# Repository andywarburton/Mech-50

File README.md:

# Mech50
A 50% ortholinear mechanical keyboard PCB with three extra keys

** PLEASE FOR THE LOVE OF GOD DO NOT ORDER THIS KEYBOARD PCB, IT'S NOT TESTED. SEE NOTES BELOW !! ** 

Update: 14th October 2024

 * Uploaded QMK Firmware

To fix:
========

* rgb wiring is wrong and doesn't work
* Uses the top right pin which makes it less compatible with other microcontrollers
* Still needs a plate
* Needs firmware for KMK / POG

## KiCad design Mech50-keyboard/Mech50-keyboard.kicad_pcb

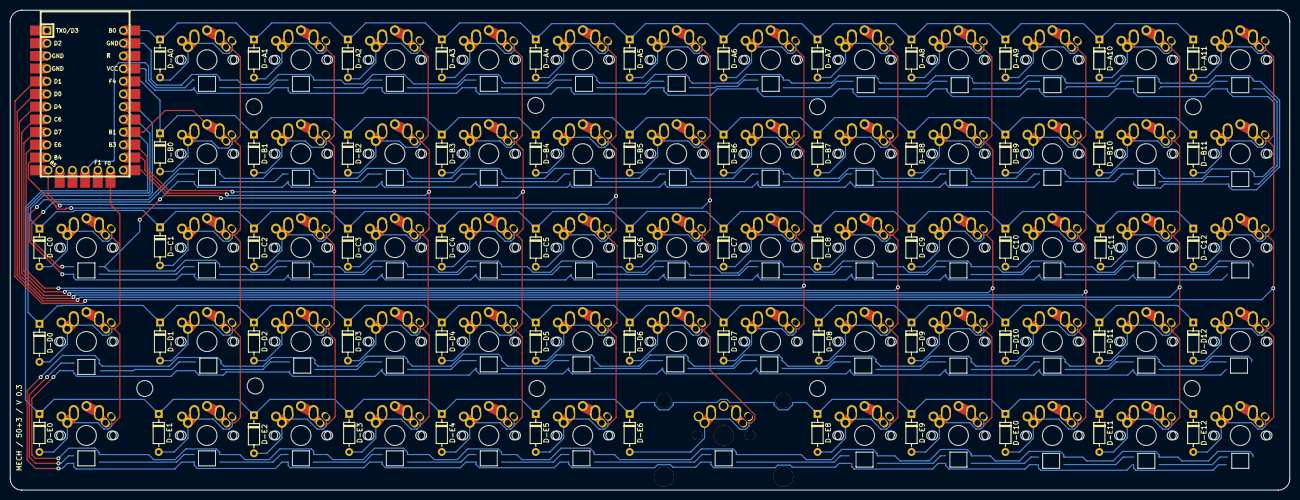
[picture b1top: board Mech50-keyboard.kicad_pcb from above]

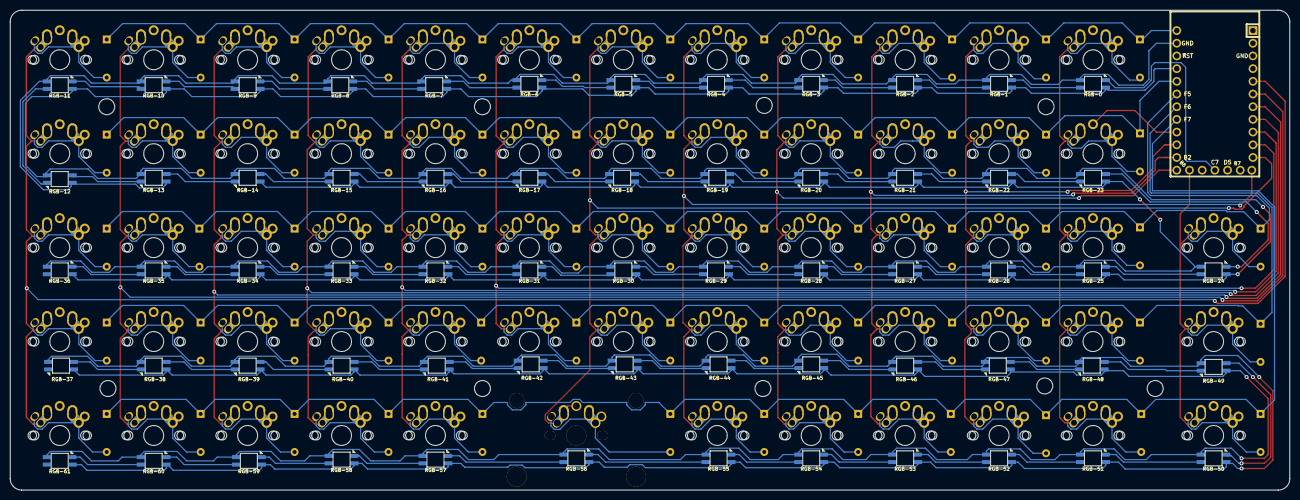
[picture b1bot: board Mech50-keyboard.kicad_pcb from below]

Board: 2 copper layers, 256.0 x 96.0 mm, 196 parts (62 on the bottom side), 141 nets.

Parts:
D-A0, D-A1, D-A2, D-A3, D-A4, D-A5, D-A6, D-A7, D-A8, D-A9, D-A10, D-A11: 1N4148; D_DO-35_SOD27_P7.62mm_Horizontal
D-B0, D-B1, D-B2, D-B3, D-B4, D-B5, D-B6, D-B7, D-B8, D-B9, D-B10, D-B11: 1N4148; D_DO-35_SOD27_P7.62mm_Horizontal
D-C0, D-C1, D-C2, D-C3, D-C4, D-C5, D-C6, D-C7, D-C8, D-C9, D-C10, D-C11, D-C12: 1N4148; D_DO-35_SOD27_P7.62mm_Horizontal
D-D0, D-D1, D-D2, D-D3, D-D4, D-D5, D-D6, D-D7, D-D8, D-D9, D-D10, D-D11, D-D12: 1N4148; D_DO-35_SOD27_P7.62mm_Horizontal
D-E0, D-E1, D-E2, D-E3, D-E4, D-E5, D-E6, D-E8, D-E9, D-E10, D-E11, D-E12: 1N4148; D_DO-35_SOD27_P7.62mm_Horizontal
H1, H2, H3, H4, H5, H10, H11, H12, H13: MountingHole; MountingHole_3.2mm_M3
RGB-0, RGB-1, RGB-2, RGB-3, RGB-4, RGB-5, RGB-6, RGB-7, RGB-8, RGB-9, RGB-10, RGB-11, RGB-12, RGB-13, RGB-14, RGB-15, RGB-16, RGB-17, RGB-18, RGB-19, RGB-20, RGB-21, RGB-22, RGB-23, RGB-24, RGB-25, RGB-26, RGB-27, RGB-28, RGB-29, RGB-30, RGB-31, RGB-32, RGB-33, RGB-34, RGB-35, RGB-36, RGB-37, RGB-38, RGB-39, RGB-40, RGB-41, RGB-42, RGB-43, RGB-44, RGB-45, RGB-46, RGB-47, RGB-48, RGB-49, RGB-50, RGB-51, RGB-52, RGB-53, RGB-54, RGB-55, RGB-56, RGB-57, RGB-58, RGB-59, RGB-60, RGB-61: SK6812MINI; SK6812-MINI-E
S-A0, S-A1, S-A2, S-A3, S-A4, S-A5, S-A6, S-A7, S-A8, S-A9, S-A10, S-A11: MX; Triple-Dual-1u-LED-flip
S-B0, S-B1, S-B2, S-B3, S-B4, S-B5, S-B6, S-B7, S-B8, S-B9, S-B10, S-B11: MX; Triple-Dual-1u-LED-flip
S-C0, S-C1, S-C2, S-C3, S-C4, S-C5, S-C6, S-C7, S-C8, S-C9, S-C10, S-C11, S-C12: MX; Triple-Dual-1u-LED-flip
S-D0, S-D1, S-D2, S-D3, S-D4, S-D5, S-D6, S-D7, S-D8, S-D9, S-D10, S-D11, S-D12: MX; Triple-Dual-1u-LED-flip
S-E0, S-E1, S-E2, S-E3, S-E4, S-E5, S-E8, S-E9, S-E10, S-E11, S-E12: MX; Triple-Dual-1u-LED-flip
S-E6: MX; Triple-Dual-2u-LED
U1: Elite-C; Elite-C-castellated-29pin-holes

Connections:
unnamed: D-A0.1, D-A1.1, D-A2.1, D-A3.1, D-A4.1, D-A5.1, D-A6.1, D-A7.1, D-A8.1, D-A9.1, D-A10.1, D-A11.1, U1.24
unnamed: D-A0.2, S-A0.1
unnamed: D-A1.2, D-B1.2, D-C2.2, D-D2.2, S-A1.1, S-B1.1, S-C2.1, S-D2.1
unnamed: D-A2.2, S-A2.1
unnamed: D-A3.2, S-A3.1
unnamed: D-A4.2, S-A4.1
unnamed: D-A5.2, S-A5.1
unnamed: D-A6.2, S-A6.1
unnamed: D-A7.2, S-A7.1
unnamed: D-A8.2, S-A8.1
unnamed: D-A9.2, S-A9.1
unnamed: D-A10.2, S-A10.1
unnamed: D-A11.2, S-A11.1
unnamed: D-B0.1, D-B1.1, D-B2.1, D-B3.1, D-B4.1, D-B5.1, D-B6.1, D-B7.1, D-B8.1, D-B9.1, D-B10.1, D-B11.1, U1.20
unnamed: D-B0.2, S-B0.1
unnamed: D-B2.2, S-B2.1
unnamed: D-B3.2, S-B3.1
unnamed: D-B4.2, S-B4.1
unnamed: D-B5.2, S-B5.1
unnamed: D-B6.2, S-B6.1
unnamed: D-B7.2, S-B7.1
unnamed: D-B8.2, S-B8.1
unnamed: D-B9.2, S-B9.1
unnamed: D-B10.2, S-B10.1
unnamed: D-B11.2, S-B11.1
unnamed: D-C0.1, D-C1.1, D-C2.1, D-C3.1, D-C4.1, D-C5.1, D-C6.1, D-C7.1, D-C8.1, D-C9.1, D-C10.1, D-C11.1, D-C12.1, U1.19
unnamed: D-C0.2, S-C0.1
unnamed: D-C1.2, S-C1.1
unnamed: D-C3.2, S-C3.1
unnamed: D-C4.2, S-C4.1
unnamed: D-C5.2, S-C5.1
unnamed: D-C6.2, S-C6.1
unnamed: D-C7.2, S-C7.1
unnamed: D-C8.2, S-C8.1
unnamed: D-C9.2, S-C9.1
unnamed: D-C10.2, S-C10.1
unnamed: D-C11.2, S-C11.1
unnamed: D-C12.2, S-C12.1
unnamed: D-D0.1, D-D1.1, D-D2.1, D-D3.1, D-D4.1, D-D5.1, D-D6.1, D-D7.1, D-D8.1, D-D9.1, D-D10.1, D-D11.1, D-D12.1, U1.18
unnamed: D-D0.2, S-D0.1
unnamed: D-D1.2, S-D1.1
unnamed: D-D3.2, S-D3.1
unnamed: D-D4.2, S-D4.1
unnamed: D-D5.2, S-D5.1
unnamed: D-D6.2, S-D6.1
unnamed: D-D7.2, S-D7.1
unnamed: D-D8.2, S-D8.1
unnamed: D-D9.2, S-D9.1
unnamed: D-D10.2, S-D10.1
unnamed: D-D11.2, S-D11.1
unnamed: D-D12.2, S-D12.1
unnamed: D-E0.1, D-E1.1, D-E2.1, D-E3.1, D-E4.1, D-E5.1, D-E6.1, D-E8.1, D-E9.1, D-E10.1, D-E11.1, D-E12.1, U1.17
unnamed: D-E0.2, S-E0.1
unnamed: D-E1.2, S-E1.1
unnamed: D-E2.2, S-E2.1
unnamed: D-E3.2, S-E3.1
unnamed: D-E4.2, S-E4.1
unnamed: D-E5.2, S-E5.1
unnamed: D-E6.2, S-E6.1
unnamed: D-E8.2, S-E8.1
unnamed: D-E9.2, S-E9.1
unnamed: D-E10.2, S-E10.1
unnamed: D-E11.2, S-E11.1
unnamed: D-E12.2, S-E12.1
unnamed: RGB-0.1, RGB-1.3
unnamed: RGB-0.2, RGB-1.2, RGB-2.2, RGB-3.2, RGB-4.2, RGB-5.2, RGB-6.2, RGB-7.2, RGB-8.2, RGB-9.2, RGB-10.2, RGB-11.2, RGB-12.2, RGB-13.2, RGB-14.2, RGB-15.2, RGB-16.2, RGB-17.2, RGB-18.2, RGB-19.2, RGB-20.2, RGB-21.2, RGB-22.2, RGB-23.2, RGB-24.2, RGB-25.2, RGB-26.2, RGB-27.2, RGB-28.2, RGB-29.2, RGB-30.2, RGB-31.2, RGB-32.2, RGB-33.2, RGB-34.2, RGB-35.2, RGB-36.2, RGB-37.2, RGB-38.2, RGB-39.2, RGB-40.2, RGB-41.2, RGB-42.2, RGB-43.2, RGB-44.2, RGB-45.2, RGB-46.2, RGB-47.2, RGB-48.2, RGB-49.2, RGB-50.2, RGB-51.2, RGB-52.2, RGB-53.2, RGB-54.2, RGB-55.2, RGB-56.2, RGB-57.2, RGB-58.2, RGB-59.2, RGB-60.2, RGB-61.2, U1.23
unnamed: RGB-0.3, U1.27
unnamed: RGB-0.4, RGB-1.4, RGB-2.4, RGB-3.4, RGB-4.4, RGB-5.4, RGB-6.4, RGB-7.4, RGB-8.4, RGB-9.4, RGB-10.4, RGB-11.4, RGB-12.4, RGB-13.4, RGB-14.4, RGB-15.4, RGB-16.4, RGB-17.4, RGB-18.4, RGB-19.4, RGB-20.4, RGB-21.4, RGB-22.4, RGB-23.4, RGB-24.4, RGB-25.4, RGB-26.4, RGB-27.4, RGB-28.4, RGB-29.4, RGB-30.4, RGB-31.4, RGB-32.4, RGB-33.4, RGB-34.4, RGB-35.4, RGB-36.4, RGB-37.4, RGB-38.4, RGB-39.4, RGB-40.4, RGB-41.4, RGB-42.4, RGB-43.4, RGB-44.4, RGB-45.4, RGB-46.4, RGB-47.4, RGB-48.4, RGB-49.4, RGB-50.4, RGB-51.4, RGB-52.4, RGB-53.4, RGB-54.4, RGB-55.4, RGB-56.4, RGB-57.4, RGB-58.4, RGB-59.4, RGB-60.4, RGB-61.4, U1.21
unnamed: RGB-1.1, RGB-2.3
unnamed: RGB-2.1, RGB-3.3
unnamed: RGB-3.1, RGB-4.3
unnamed: RGB-4.1, RGB-5.3
unnamed: RGB-5.1, RGB-6.3
unnamed: RGB-6.1, RGB-7.3
unnamed: RGB-7.1, RGB-8.3
unnamed: RGB-8.1, RGB-9.3
unnamed: RGB-10.1, RGB-11.3
unnamed: RGB-9.1, RGB-10.3
unnamed: RGB-11.1, RGB-12.3
unnamed: RGB-12.1, RGB-13.3
unnamed: RGB-13.1, RGB-14.3
unnamed: RGB-14.1, RGB-15.3
unnamed: RGB-15.1, RGB-16.3
unnamed: RGB-16.1, RGB-17.3
unnamed: RGB-17.1, RGB-18.3
unnamed: RGB-18.1, RGB-19.3
unnamed: RGB-19.1, RGB-20.3
unnamed: RGB-20.1, RGB-21.3
unnamed: RGB-21.1, RGB-22.3
unnamed: RGB-22.1, RGB-23.3
unnamed: RGB-23.1, RGB-24.3
unnamed: RGB-24.1, RGB-25.3
unnamed: RGB-25.1, RGB-26.3
unnamed: RGB-26.1, RGB-27.3
unnamed: RGB-27.1, RGB-28.3
unnamed: RGB-28.1, RGB-29.3
unnamed: RGB-29.1, RGB-30.3
unnamed: RGB-30.1, RGB-31.3
unnamed: RGB-31.1, RGB-32.3
unnamed: RGB-32.1, RGB-33.3
unnamed: RGB-33.1, RGB-34.3
unnamed: RGB-34.1, RGB-35.3
unnamed: RGB-35.1, RGB-36.3
unnamed: RGB-36.1, RGB-37.3
unnamed: RGB-37.1, RGB-38.3
unnamed: RGB-38.1, RGB-39.3
unnamed: RGB-39.1, RGB-40.3
unnamed: RGB-40.1, RGB-41.3
unnamed: RGB-41.1, RGB-42.3
unnamed: RGB-42.1, RGB-43.3
unnamed: RGB-43.1, RGB-44.3
unnamed: RGB-44.1, RGB-45.3
unnamed: RGB-45.1, RGB-46.3
unnamed: RGB-46.1, RGB-47.3
unnamed: RGB-47.1, RGB-48.3
unnamed: RGB-48.1, RGB-49.3
unnamed: RGB-49.1, RGB-50.3
unnamed: RGB-50.1, RGB-51.3
unnamed: RGB-51.1, RGB-52.3
unnamed: RGB-52.1, RGB-53.3
unnamed: RGB-53.1, RGB-54.3
unnamed: RGB-54.1, RGB-55.3
unnamed: RGB-55.1, RGB-56.3
unnamed: RGB-56.1, RGB-57.3
unnamed: RGB-57.1, RGB-58.3
unnamed: RGB-58.1, RGB-59.3
unnamed: RGB-59.1, RGB-60.3
unnamed: RGB-60.1, RGB-61.3
unnamed: S-A0.2, S-B0.2, S-C1.2, S-D1.2, S-E1.2, U1.16
unnamed: S-A1.2, S-B1.2, S-C2.2, S-D2.2, S-E2.2, U1.15
unnamed: S-A2.2, S-B2.2, S-C3.2, S-D3.2, S-E3.2, U1.14
unnamed: S-A3.2, S-B3.2, S-C4.2, S-D4.2, S-E4.2, U1.13
unnamed: S-A4.2, S-B4.2, S-C5.2, S-D5.2, S-E5.2, U1.12
unnamed: S-A5.2, S-B5.2, S-C6.2, S-D6.2, S-E6.2, U1.11
unnamed: S-A6.2, S-B6.2, S-C7.2, S-D7.2, U1.10
unnamed: S-A7.2, S-B7.2, S-C8.2, S-D8.2, S-E8.2, U1.9
unnamed: S-A8.2, S-B8.2, S-C9.2, S-D9.2, S-E9.2, U1.8
unnamed: S-A9.2, S-B9.2, S-C10.2, S-D10.2, S-E10.2, U1.7
unnamed: S-A10.2, S-B10.2, S-C11.2, S-D11.2, S-E11.2, U1.6
unnamed: S-A11.2, S-B11.2, S-C12.2, S-D12.2, S-E12.2, U1.5
unnamed: S-C0.2, S-D0.2, S-E0.2, U1.29

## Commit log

2021-04-11 added all the things
2021-11-22 fixed some bugs with low profile switches
2024-10-14 Added QMK Firmware
